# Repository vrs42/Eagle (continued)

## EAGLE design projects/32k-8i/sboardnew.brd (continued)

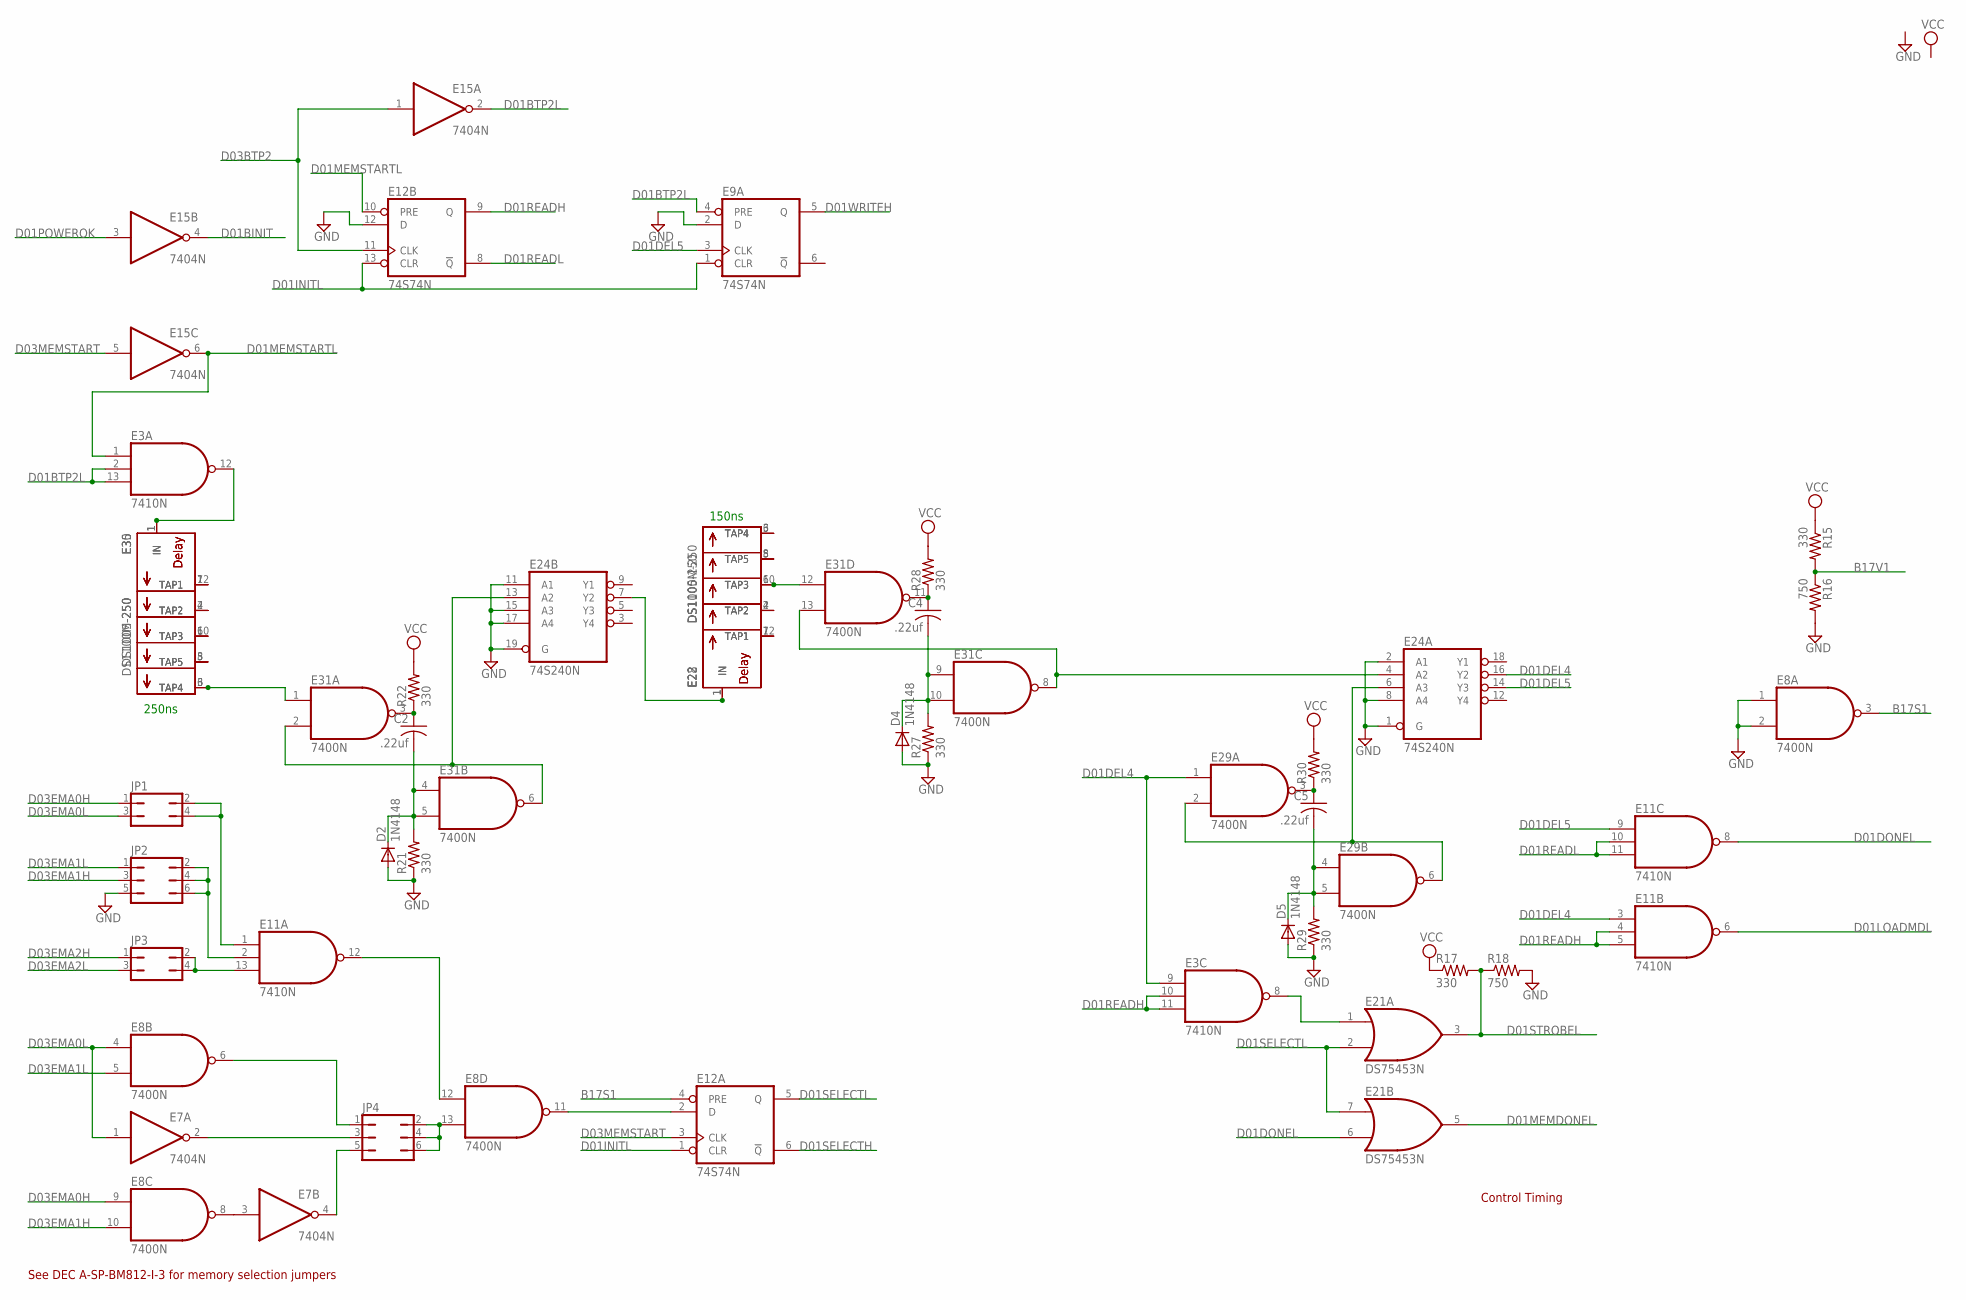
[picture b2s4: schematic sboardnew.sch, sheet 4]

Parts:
C2, C4, C5: .22uf; C050-025X075
D2, D4, D5: 1N4148; DO35-10
E3, E11: 7410N; DIL14
E7, E15: 7404N; DIL14
E8, E29, E31: 7400N; DIL14
E9, E12: 74S74N; DIL14
E21: DS75453N; DIL08
E22, E35: DS1100M-250; DIL08
E24: 74S240N; DIL20
E28, E30: DS1005-250; DIL14
JP1, JP3: JP2Q
JP2, JP4: JP3Q
R15, R17, R21, R22, R27, R28, R29, R30: 330; 0207/10
R16, R18: 750; 0207/10

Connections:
B17S1: E8.3 (O), E12.4 (PRE); also elsewhere on the board
B17V1: R15.2, R16.1; also elsewhere on the board
D01BINIT: E15.4 (O); also elsewhere on the board
D01BTP2L: E3.2 (I1), E3.13 (I2), E9.4 (PRE), E15.2 (O)
D01DEL2X: E22.1 (IN), E24.7 (Y2), E28.1 (IN)
D01DEL4: E3.9 (I0), E11.3 (I0), E24.16 (Y2), E29.1 (I0)
D01DEL5: E9.3 (CLK), E11.9 (I0), E24.14 (Y3)
D01DONEL: E11.8 (O), E21.6 (I1)
D01INITL: E9.1 (CLR), E12.1 (CLR), E12.13 (CLR); also elsewhere on the board
D01LOADMDL: E11.6 (O); also elsewhere on the board
D01MEMDONEL: E21.5 (O); also elsewhere on the board
D01MEMSTARTL: E3.1 (I0), E12.10 (PRE), E15.6 (O)
D01POWEROK: E15.3 (I); also elsewhere on the board
D01READH: E3.10 (I1), E3.11 (I2), E11.4 (I1), E11.5 (I2), E12.9 (Q)
D01READL: E11.10 (I1), E11.11 (I2), E12.8 (!Q); also elsewhere on the board
D01SELECTH: E12.6 (!Q); also elsewhere on the board
D01SELECTL: E12.5 (Q), E21.2 (I1), E21.7 (I0)
D01SELL: E8.11 (O), E12.2 (D)
D01STROBEL: E21.3 (O), R17.2, R18.1; also elsewhere on the board
D01WRITEH: E9.5 (Q); also elsewhere on the board
D03BTP2: E12.11 (CLK), E15.1 (I); also elsewhere on the board
D03EMA0H: E8.9 (I0), JP1.1; also elsewhere on the board
D03EMA0L: E7.1 (I), E8.4 (I0), JP1.3; also elsewhere on the board
D03EMA1H: E8.10 (I1), JP2.3; also elsewhere on the board
D03EMA1L: E8.5 (I1), JP2.1; also elsewhere on the board
D03EMA2H: JP3.1; also elsewhere on the board
D03EMA2L: JP3.3; also elsewhere on the board
D03MEMSTART: E12.3 (CLK), E15.5 (I); also elsewhere on the board
GND: D2.A, D4.A, D5.A, E3.7 (GND), E7.7 (GND), E8.1 (I0), E8.2 (I1), E8.7 (GND), E9.2 (D), E9.7 (GND), E11.7 (GND), E12.7 (GND), E12.12 (D), E15.7 (GND), E21.4 (GND), E22.4 (GND), E24.1 (G), E24.2 (A1), E24.8 (A4), E24.10 (GND), E24.11 (A1), E24.15 (A3), E24.17 (A4), E24.19 (G), E28.7 (GND), E29.7 (GND), E30.7 (GND), E31.7 (GND), E35.4 (GND), JP2.5, R16.2, R18.2, R21.1, R27.1, R29.1; also elsewhere on the board
unnamed: E22.2 (TAP2), E28.4 (TAP2)
unnamed: C5.2, D5.C, E29.4 (I0), E29.5 (I1), R29.2
unnamed: E8.13 (I1), JP4.2, JP4.4, JP4.6
unnamed: C2.2, D2.C, E31.4 (I0), E31.5 (I1), R21.2
unnamed: E30.12 (TAP1), E35.7 (TAP1)
unnamed: C2.1, E31.3 (O), R22.1
unnamed: E24.13 (A2), E31.2 (I1), E31.6 (O)
unnamed: E30.6 (TAP4), E31.1 (I0), E35.3 (TAP4)
unnamed: C4.2, D4.C, E31.9 (I0), E31.10 (I1), R27.2
unnamed: C4.1, E31.11 (O), R28.1
unnamed: E3.12 (O), E30.1 (IN), E35.1 (IN)
unnamed: E24.4 (A2), E31.8 (O), E31.13 (I1)
unnamed: E22.6 (TAP3), E28.10 (TAP3), E31.12 (I0)
unnamed: C5.1, E29.3 (O), R30.1
unnamed: E24.6 (A3), E29.2 (I1), E29.6 (O)
unnamed: E22.7 (TAP1), E28.12 (TAP1)
unnamed: E22.3 (TAP4), E28.6 (TAP4)
unnamed: E22.5 (TAP5), E28.8 (TAP5)
unnamed: E30.4 (TAP2), E35.2 (TAP2)
unnamed: E30.10 (TAP3), E35.6 (TAP3)
unnamed: E30.8 (TAP5), E35.5 (TAP5)
unnamed: E8.6 (O), JP4.1
unnamed: E3.8 (O), E21.1 (I0)
unnamed: E7.2 (O), JP4.3
unnamed: E7.3 (I), E8.8 (O)
unnamed: E7.4 (O), JP4.5
unnamed: E11.13 (I2), JP3.2, JP3.4
unnamed: E11.2 (I1), JP2.2, JP2.4, JP2.6
unnamed: E11.1 (I0), JP1.2, JP1.4
unnamed: E8.12 (I0), E11.12 (O)
VCC: E3.14 (VCC), E7.14 (VCC), E8.14 (VCC), E9.14 (VCC), E11.14 (VCC), E12.14 (VCC), E15.14 (VCC), E21.8 (VCC), E22.8 (VCC), E24.20 (VCC), E28.14 (VCC), E29.14 (VCC), E30.14 (VCC), E31.14 (VCC), E35.8 (VCC), R15.1, R17.1, R22.2, R28.2, R30.2; also elsewhere on the board

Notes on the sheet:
Control Timing
See DEC A-SP-BM812-I-3 for memory selection jumpers
250ns
150ns

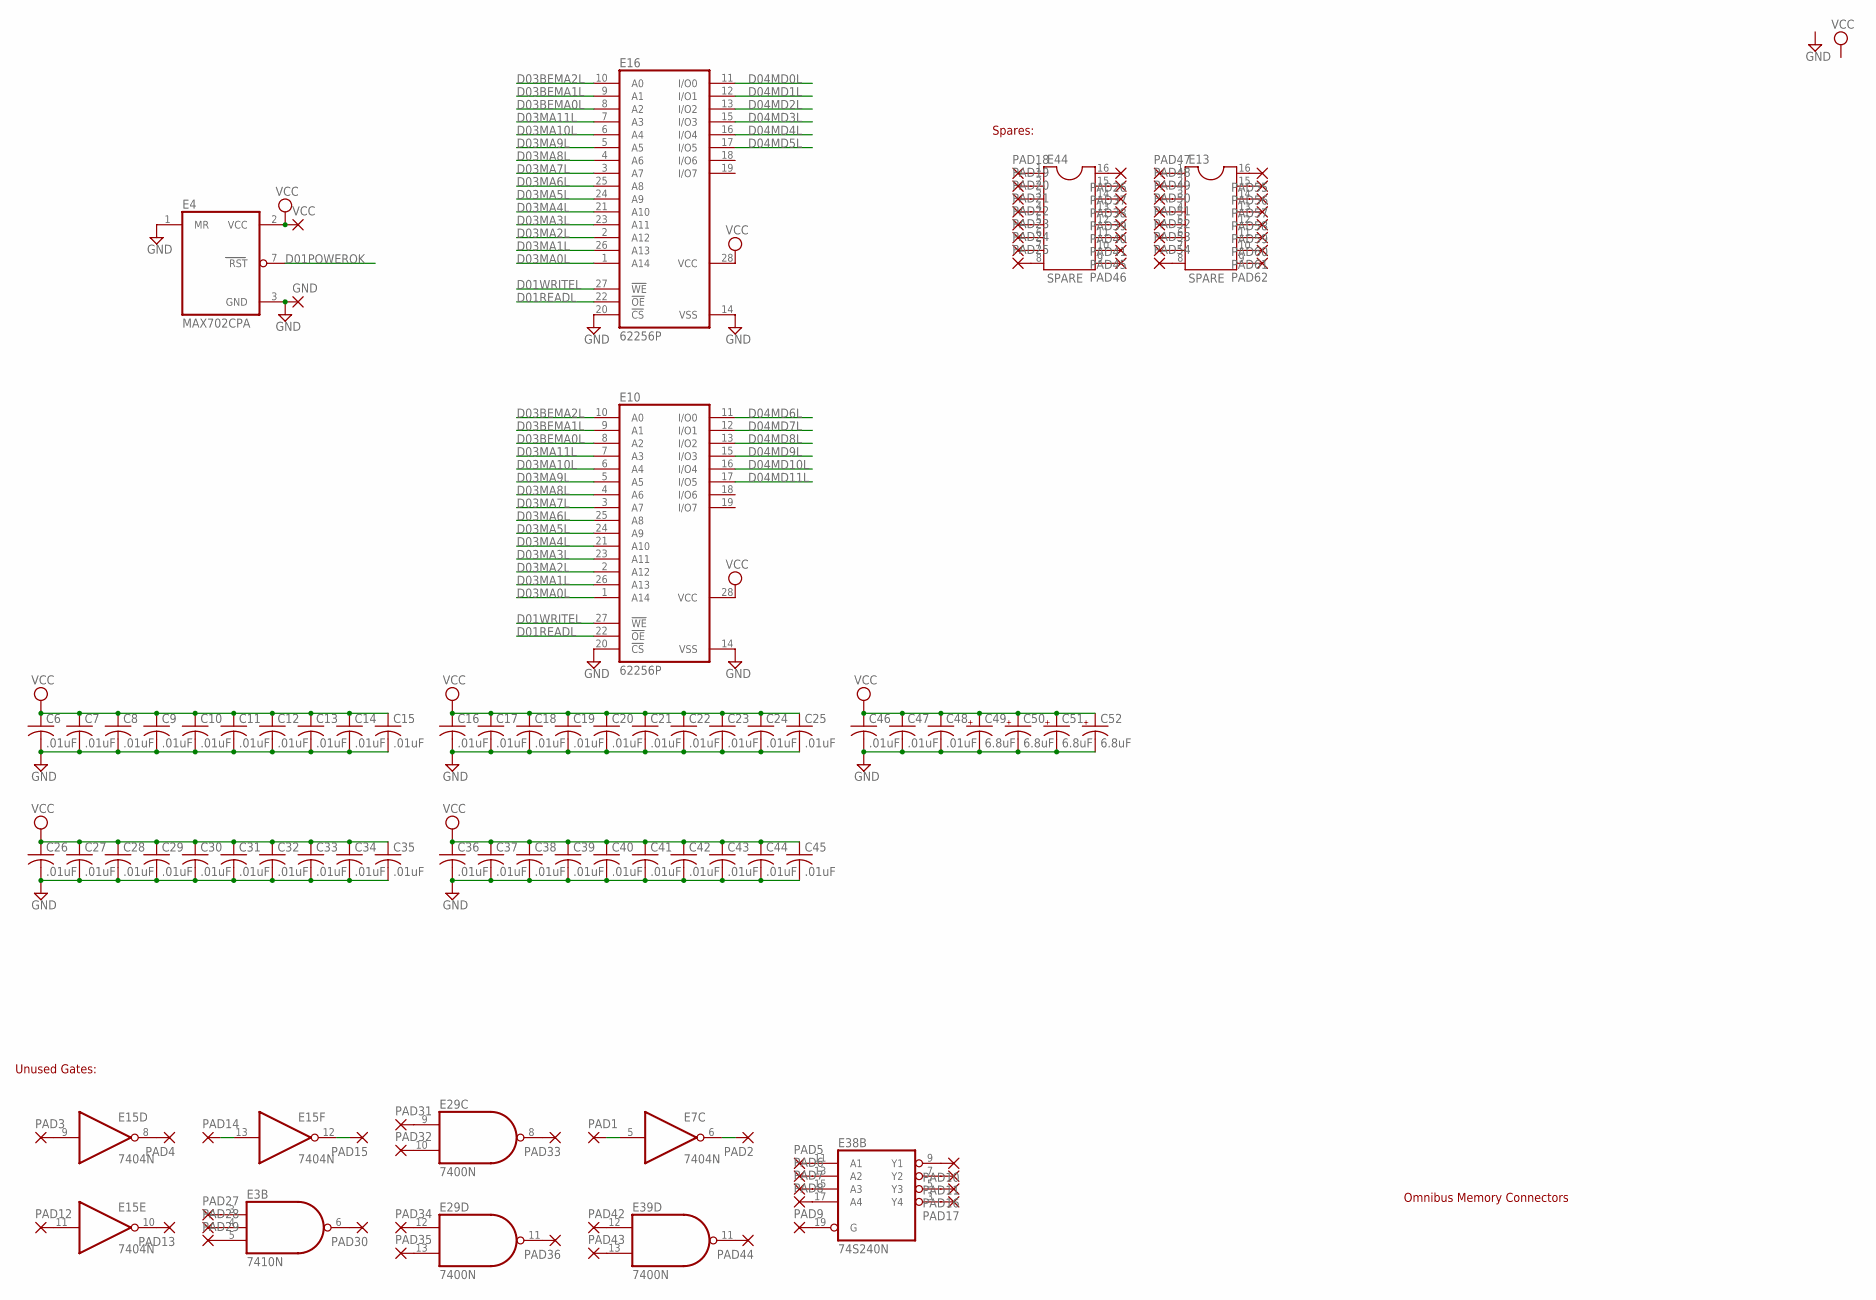
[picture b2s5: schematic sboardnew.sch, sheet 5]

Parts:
C6, C7, C8, C9, C10, C11, C12, C13, C14, C15, C16, C17, C18, C19, C20, C21, C22, C23, C24, C25, C26, C27, C28, C29, C30, C31, C32, C33, C34, C35, C36, C37, C38, C39, C40, C41, C42, C43, C44, C45, C46, C47, C48: .01uF; C050-025X075
C49, C50, C51, C52: 6.8uF; E22-6
E3: 7410N; DIL14
E4: MAX702CPA; DIL08
E7, E15: 7404N; DIL14
E10, E16: 62256P; DIL28-6
E13, E44: SPARE; DIL16
E29, E39: 7400N; DIL14
E38: 74S240N; DIL20
GND: 2,15/1,0
PAD1, PAD2, PAD3, PAD4, PAD5, PAD6, PAD7, PAD8, PAD9, PAD10, PAD11, PAD12, PAD13, PAD14, PAD15, PAD16, PAD17, PAD18, PAD19, PAD20, PAD21, PAD22, PAD23, PAD24, PAD25, PAD26, PAD27, PAD28, PAD29, PAD30, PAD31, PAD32, PAD33, PAD34, PAD35, PAD36, PAD37, PAD38, PAD39, PAD40, PAD41, PAD42, PAD43, PAD44, PAD45, PAD46, PAD47, PAD48, PAD49, PAD50, PAD51, PAD52, PAD53, PAD54, PAD55, PAD56, PAD57, PAD58, PAD59, PAD60, PAD61, PAD62: 1,6/0,8
VCC: 2,15/1,0

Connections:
D01POWEROK: E4.7 (RST); also elsewhere on the board
D01READL: E10.22 (!OE), E16.22 (!OE); also elsewhere on the board
D01WRITEL: E10.27 (!WE), E16.27 (!WE); also elsewhere on the board
D03BEMA0L: E10.8 (A2), E16.8 (A2); also elsewhere on the board
D03BEMA1L: E10.9 (A1), E16.9 (A1); also elsewhere on the board
D03BEMA2L: E10.10 (A0), E16.10 (A0); also elsewhere on the board
D03MA0L: E10.1 (A14), E16.1 (A14); also elsewhere on the board
D03MA1L: E10.26 (A13), E16.26 (A13); also elsewhere on the board
D03MA2L: E10.2 (A12), E16.2 (A12); also elsewhere on the board
D03MA3L: E10.23 (A11), E16.23 (A11); also elsewhere on the board
D03MA4L: E10.21 (A10), E16.21 (A10); also elsewhere on the board
D03MA5L: E10.24 (A9), E16.24 (A9); also elsewhere on the board
D03MA6L: E10.25 (A8), E16.25 (A8); also elsewhere on the board
D03MA7L: E10.3 (A7), E16.3 (A7); also elsewhere on the board
D03MA8L: E10.4 (A6), E16.4 (A6); also elsewhere on the board
D03MA9L: E10.5 (A5), E16.5 (A5); also elsewhere on the board
D03MA10L: E10.6 (A4), E16.6 (A4); also elsewhere on the board
D03MA11L: E10.7 (A3), E16.7 (A3); also elsewhere on the board
D04MD0L: E16.11 (I/O0); also elsewhere on the board
D04MD1L: E16.12 (I/O1); also elsewhere on the board
D04MD2L: E16.13 (I/O2); also elsewhere on the board
D04MD3L: E16.15 (I/O3); also elsewhere on the board
D04MD4L: E16.16 (I/O4); also elsewhere on the board
D04MD5L: E16.17 (I/O5); also elsewhere on the board
D04MD6L: E10.11 (I/O0); also elsewhere on the board
D04MD7L: E10.12 (I/O1); also elsewhere on the board
D04MD8L: E10.13 (I/O2); also elsewhere on the board
D04MD9L: E10.15 (I/O3); also elsewhere on the board
D04MD10L: E10.16 (I/O4); also elsewhere on the board
D04MD11L: E10.17 (I/O5); also elsewhere on the board
GND: C6.2, C7.2, C8.2, C9.2, C10.2, C11.2, C12.2, C13.2, C14.2, C15.2, C16.2, C17.2, C18.2, C19.2, C20.2, C21.2, C22.2, C23.2, C24.2, C25.2, C26.2, C27.2, C28.2, C29.2, C30.2, C31.2, C32.2, C33.2, C34.2, C35.2, C36.2, C37.2, C38.2, C39.2, C40.2, C41.2, C42.2, C43.2, C44.2, C45.2, C46.2, C47.2, C48.2, C49.-, C50.-, C51.-, C52.-, E3.7 (GND), E4.1 (MR), E4.3 (GND), E7.7 (GND), E10.14 (VSS), E10.20 (!CS), E15.7 (GND), E16.14 (VSS), E16.20 (!CS), E29.7 (GND), E38.10 (GND), E39.7 (GND), GND.1; also elsewhere on the board
unnamed: E7.5 (I), PAD1.1
unnamed: E7.6 (O), PAD2.1
unnamed: E15.9 (I), PAD3.1
unnamed: E15.8 (O), PAD4.1
unnamed: E38.11 (A1), PAD5.1
unnamed: E38.13 (A2), PAD6.1
unnamed: E38.15 (A3), PAD7.1
unnamed: E38.19 (G), PAD9.1
unnamed: E38.9 (Y1), PAD10.1
unnamed: E38.7 (Y2), PAD11.1
unnamed: E38.5 (Y3), PAD16.1
unnamed: E38.3 (Y4), PAD17.1
unnamed: E38.17 (A4), PAD8.1
unnamed: E44.1, PAD18.1
unnamed: E44.2, PAD19.1
unnamed: E44.3, PAD20.1
unnamed: E44.4, PAD21.1
unnamed: E15.11 (I), PAD12.1
unnamed: E15.10 (O), PAD13.1
unnamed: E15.13 (I), PAD14.1
unnamed: E15.12 (O), PAD15.1
unnamed: E44.5, PAD22.1
unnamed: E44.6, PAD23.1
unnamed: E44.7, PAD24.1
unnamed: E44.8, PAD25.1
unnamed: E44.16, PAD26.1
unnamed: E44.15, PAD37.1
unnamed: E44.14, PAD38.1
unnamed: E44.13, PAD39.1
unnamed: E44.12, PAD40.1
unnamed: E44.11, PAD41.1
unnamed: E44.10, PAD45.1
unnamed: E3.3 (I0), PAD27.1
unnamed: E3.4 (I1), PAD28.1
unnamed: E3.5 (I2), PAD29.1
unnamed: E3.6 (O), PAD30.1
unnamed: E29.9 (I0), PAD31.1
unnamed: E29.10 (I1), PAD32.1
unnamed: E29.8 (O), PAD33.1
unnamed: E29.12 (I0), PAD34.1
unnamed: E29.13 (I1), PAD35.1
unnamed: E29.11 (O), PAD36.1
unnamed: E44.9, PAD46.1
unnamed: E13.1, PAD47.1
unnamed: E13.2, PAD48.1
unnamed: E13.3, PAD49.1
unnamed: E13.4, PAD50.1
unnamed: E39.12 (I0), PAD42.1
unnamed: E39.13 (I1), PAD43.1
unnamed: E39.11 (O), PAD44.1
unnamed: E13.5, PAD51.1
unnamed: E13.6, PAD52.1
unnamed: E13.7, PAD53.1
unnamed: E13.8, PAD54.1
unnamed: E13.16, PAD55.1
unnamed: E13.15, PAD56.1
unnamed: E13.14, PAD57.1
unnamed: E13.13, PAD58.1
unnamed: E13.12, PAD59.1
unnamed: E13.11, PAD60.1
unnamed: E13.10, PAD61.1
unnamed: E13.9, PAD62.1
VCC: C6.1, C7.1, C8.1, C9.1, C10.1, C11.1, C12.1, C13.1, C14.1, C15.1, C16.1, C17.1, C18.1, C19.1, C20.1, C21.1, C22.1, C23.1, C24.1, C25.1, C26.1, C27.1, C28.1, C29.1, C30.1, C31.1, C32.1, C33.1, C34.1, C35.1, C36.1, C37.1, C38.1, C39.1, C40.1, C41.1, C42.1, C43.1, C44.1, C45.1, C46.1, C47.1, C48.1, C49.+, C50.+, C51.+, C52.+, E3.14 (VCC), E4.2 (VCC), E7.14 (VCC), E10.28 (VCC), E15.14 (VCC), E16.28 (VCC), E29.14 (VCC), E38.20 (VCC), E39.14 (VCC), VCC.1; also elsewhere on the board

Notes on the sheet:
Omnibus Memory Connectors
Unused Gates:
Spares:

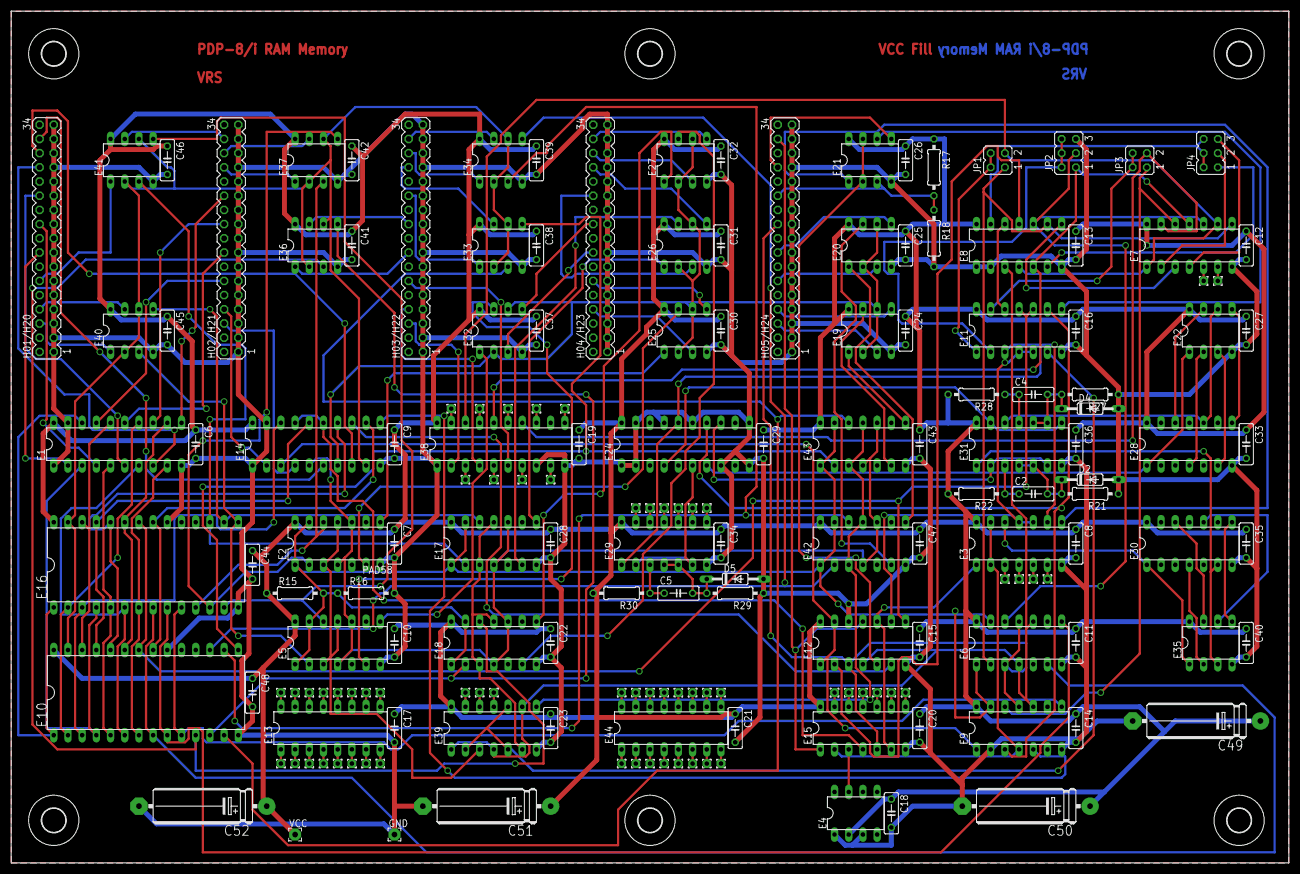
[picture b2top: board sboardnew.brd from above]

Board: 2 copper layers, 228.6 x 152.4 mm, 185 parts (0 on the bottom side), 206 nets.

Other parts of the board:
U$20, U$66, U$67, U$82, U$83, U$86: 4,3

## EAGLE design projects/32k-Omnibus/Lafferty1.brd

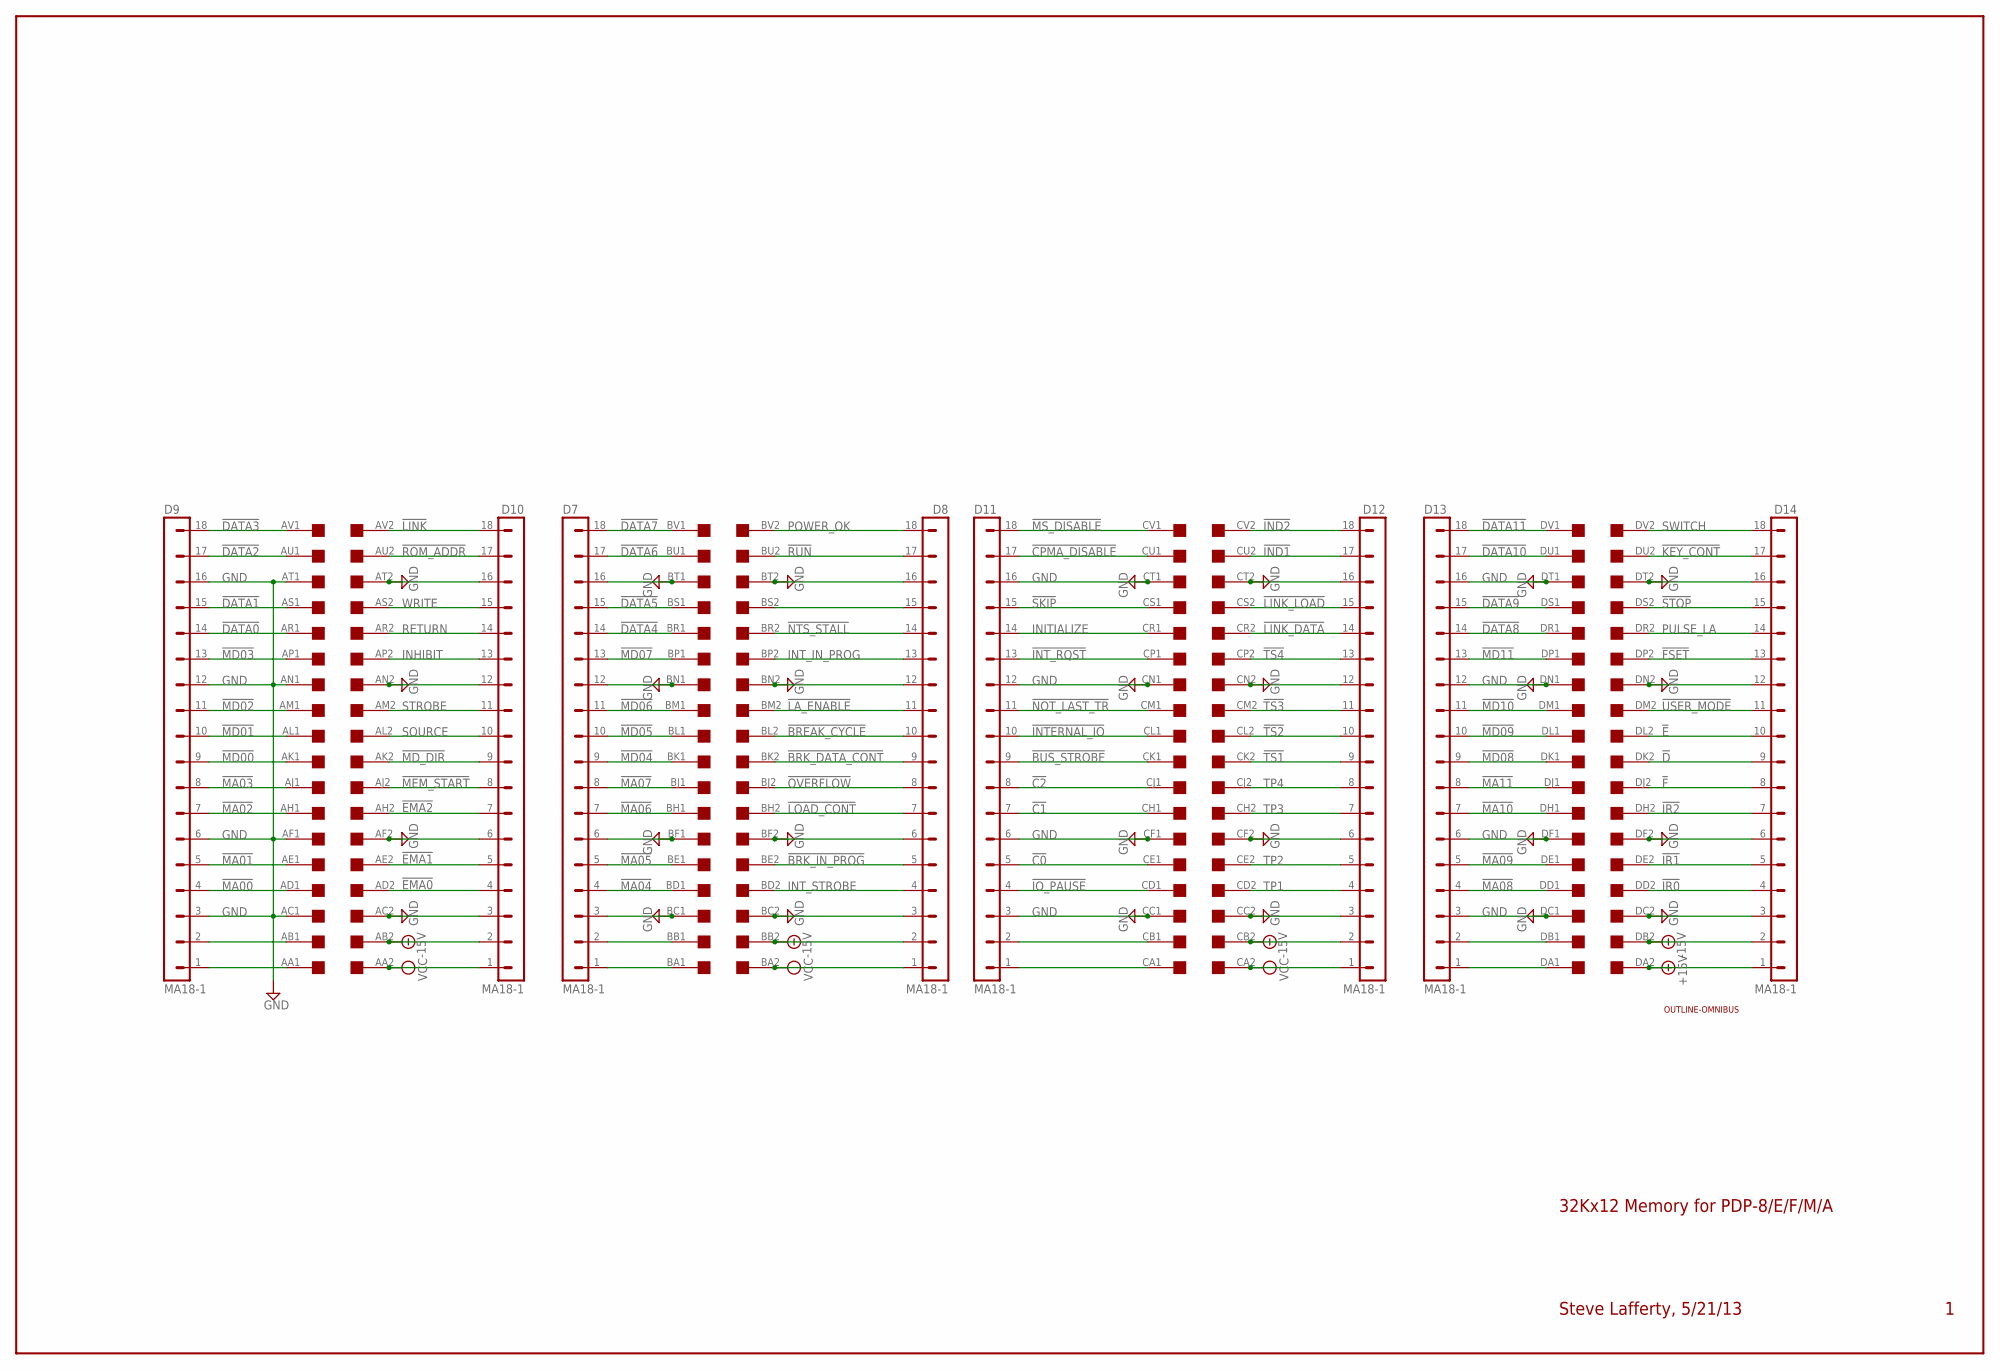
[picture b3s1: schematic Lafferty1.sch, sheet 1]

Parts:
D7, D8, D9, D10, D11, D12, D13, D14: MA18-1
U$1: OUTLINE-OMNIBUS; OMNIBUS
U$2: QUAD; EDGE-CON8

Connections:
!BREAK_CYCLE: D8.10, U$2.BL2
!BRK_DATA_CONT: D8.9, U$2.BK2
!BRK_IN_PROG: D8.5, U$2.BE2
!BUS_STROBE: D11.9, U$2.CK1
!C0: D11.5, U$2.CE1
!C1: D11.7, U$2.CH1
!C2: D11.8, U$2.CJ1
!CPMA_DISABLE: D11.17, U$2.CU1
!D: D14.9, U$2.DK2
!DATA0: D9.14, U$2.AR1
!DATA1: D9.15, U$2.AS1
!DATA2: D9.17, U$2.AU1
!DATA3: D9.18, U$2.AV1
!DATA4: D7.14, U$2.BR1
!DATA5: D7.15, U$2.BS1
!DATA6: D7.17, U$2.BU1
!DATA7: D7.18, U$2.BV1
!DATA8: D13.14, U$2.DR1
!DATA9: D13.15, U$2.DS1
!DATA10: D13.17, U$2.DU1
!DATA11: D13.18, U$2.DV1
!E: D14.10, U$2.DL2
!EMA0: D10.4, U$2.AD2; also elsewhere on the board
!EMA1: D10.5, U$2.AE2; also elsewhere on the board
!EMA2: D10.7, U$2.AH2; also elsewhere on the board
!F: D14.8, U$2.DJ2
!FSET: D14.13, U$2.DP2
!IND1: D12.17, U$2.CU2
!IND2: D12.18, U$2.CV2
!INTERNAL_IO: D11.10, U$2.CL1
!INT_RQST: D11.13, U$2.CP1
!IO_PAUSE: D11.4, U$2.CD1
!IR0: D14.4, U$2.DD2
!IR1: D14.5, U$2.DE2
!IR2: D14.7, U$2.DH2
!KEY_CONT: D14.17, U$2.DU2
!LA_ENABLE: D8.11, U$2.BM2
!LINK: D10.18, U$2.AV2
!LINK_DATA: D12.14, U$2.CR2
!LINK_LOAD: D12.15, U$2.CS2
!LOAD_CONT: D8.7, U$2.BH2
!MA00: D9.4, U$2.AD1; also elsewhere on the board
!MA01: D9.5, U$2.AE1; also elsewhere on the board
!MA02: D9.7, U$2.AH1; also elsewhere on the board
!MA03: D9.8, U$2.AJ1; also elsewhere on the board
!MA04: D7.4, U$2.BD1; also elsewhere on the board
!MA05: D7.5, U$2.BE1; also elsewhere on the board
!MA06: D7.7, U$2.BH1; also elsewhere on the board
!MA07: D7.8, U$2.BJ1; also elsewhere on the board
!MA08: D13.4, U$2.DD1; also elsewhere on the board
!MA09: D13.5, U$2.DE1; also elsewhere on the board
!MA10: D13.7, U$2.DH1; also elsewhere on the board
!MA11: D13.8, U$2.DJ1; also elsewhere on the board
!MD00: D9.9, U$2.AK1; also elsewhere on the board
!MD01: D9.10, U$2.AL1; also elsewhere on the board
!MD02: D9.11, U$2.AM1; also elsewhere on the board
!MD03: D9.13, U$2.AP1; also elsewhere on the board
!MD04: D7.9, U$2.BK1; also elsewhere on the board
!MD05: D7.10, U$2.BL1; also elsewhere on the board
!MD06: D7.11, U$2.BM1; also elsewhere on the board
!MD07: D7.13, U$2.BP1; also elsewhere on the board
!MD08: D13.9, U$2.DK1; also elsewhere on the board
!MD09: D13.10, U$2.DL1; also elsewhere on the board
!MD10: D13.11, U$2.DM1; also elsewhere on the board
!MD11: D13.13, U$2.DP1; also elsewhere on the board
!MD_DIR: D10.9, U$2.AK2; also elsewhere on the board
!MEM_START: D10.8, U$2.AJ2
!MS_DISABLE: D11.18, U$2.CV1
!NOT_LAST_TR: D11.11, U$2.CM1
!NTS_STALL: D8.14, U$2.BR2
!OVERFLOW: D8.8, U$2.BJ2
!ROM_ADDR: D10.17, U$2.AU2; also elsewhere on the board
!RUN: D8.17, U$2.BU2
!SKIP: D11.15, U$2.CS1
!STOP: D14.15, U$2.DS2
!TS1: D12.9, U$2.CK2
!TS2: D12.10, U$2.CL2
!TS3: D12.11, U$2.CM2
!TS4: D12.13, U$2.CP2
!USER_MODE: D14.11, U$2.DM2
+15V: D14.1, U$2.DA2
-15V: D8.2, D10.2, D12.2, D14.2, U$2.AB2, U$2.BB2, U$2.CB2, U$2.DB2
GND: D7.3, D7.6, D7.12, D7.16, D8.3, D8.6, D8.12, D8.16, D9.3, D9.6, D9.12, D9.16, D10.3, D10.6, D10.12, D10.16, D11.3, D11.6, D11.12, D11.16, D12.3, D12.6, D12.12, D12.16, D13.3, D13.6, D13.12, D13.16, D14.3, D14.6, D14.12, D14.16, U$2.AC1, U$2.AC2, U$2.AF1, U$2.AF2, U$2.AN1, U$2.AN2, U$2.AT1, U$2.AT2, U$2.BC1, U$2.BC2, U$2.BF1, U$2.BF2, U$2.BN1, U$2.BN2, U$2.BT1, U$2.BT2, U$2.CC1, U$2.CC2, U$2.CF1, U$2.CF2, U$2.CN1, U$2.CN2, U$2.CT1, U$2.CT2, U$2.DC1, U$2.DC2, U$2.DF1, U$2.DF2, U$2.DN1, U$2.DN2, U$2.DT1, U$2.DT2; also elsewhere on the board
INHIBIT: D10.13, U$2.AP2
INITIALIZE: D11.14, U$2.CR1
INT_IN_PROG: D8.13, U$2.BP2
INT_STROBE: D8.4, U$2.BD2
unnamed: D9.2, U$2.AB1
unnamed: D9.1, U$2.AA1
unnamed: D7.2, U$2.BB1
unnamed: D7.1, U$2.BA1
unnamed: D11.1, U$2.CA1
unnamed: D8.15, U$2.BS2
unnamed: D11.2, U$2.CB1
unnamed: D13.1, U$2.DA1
unnamed: D13.2, U$2.DB1
POWER_OK: D8.18, U$2.BV2; also elsewhere on the board
PULSE_LA: D14.14, U$2.DR2
RETURN: D10.14, U$2.AR2
SOURCE: D10.10, U$2.AL2; also elsewhere on the board
STROBE: D10.11, U$2.AM2
SWITCH: D14.18, U$2.DV2
TP1: D12.4, U$2.CD2
TP2: D12.5, U$2.CE2
TP3: D12.7, U$2.CH2
TP4: D12.8, U$2.CJ2
VCC: D8.1, D10.1, D12.1, U$2.AA2, U$2.BA2, U$2.CA2; also elsewhere on the board
WRITE: D10.15, U$2.AS2; also elsewhere on the board

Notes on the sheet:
32Kx12 Memory for PDP-8/E/F/M/A
Steve Lafferty, 5/21/13

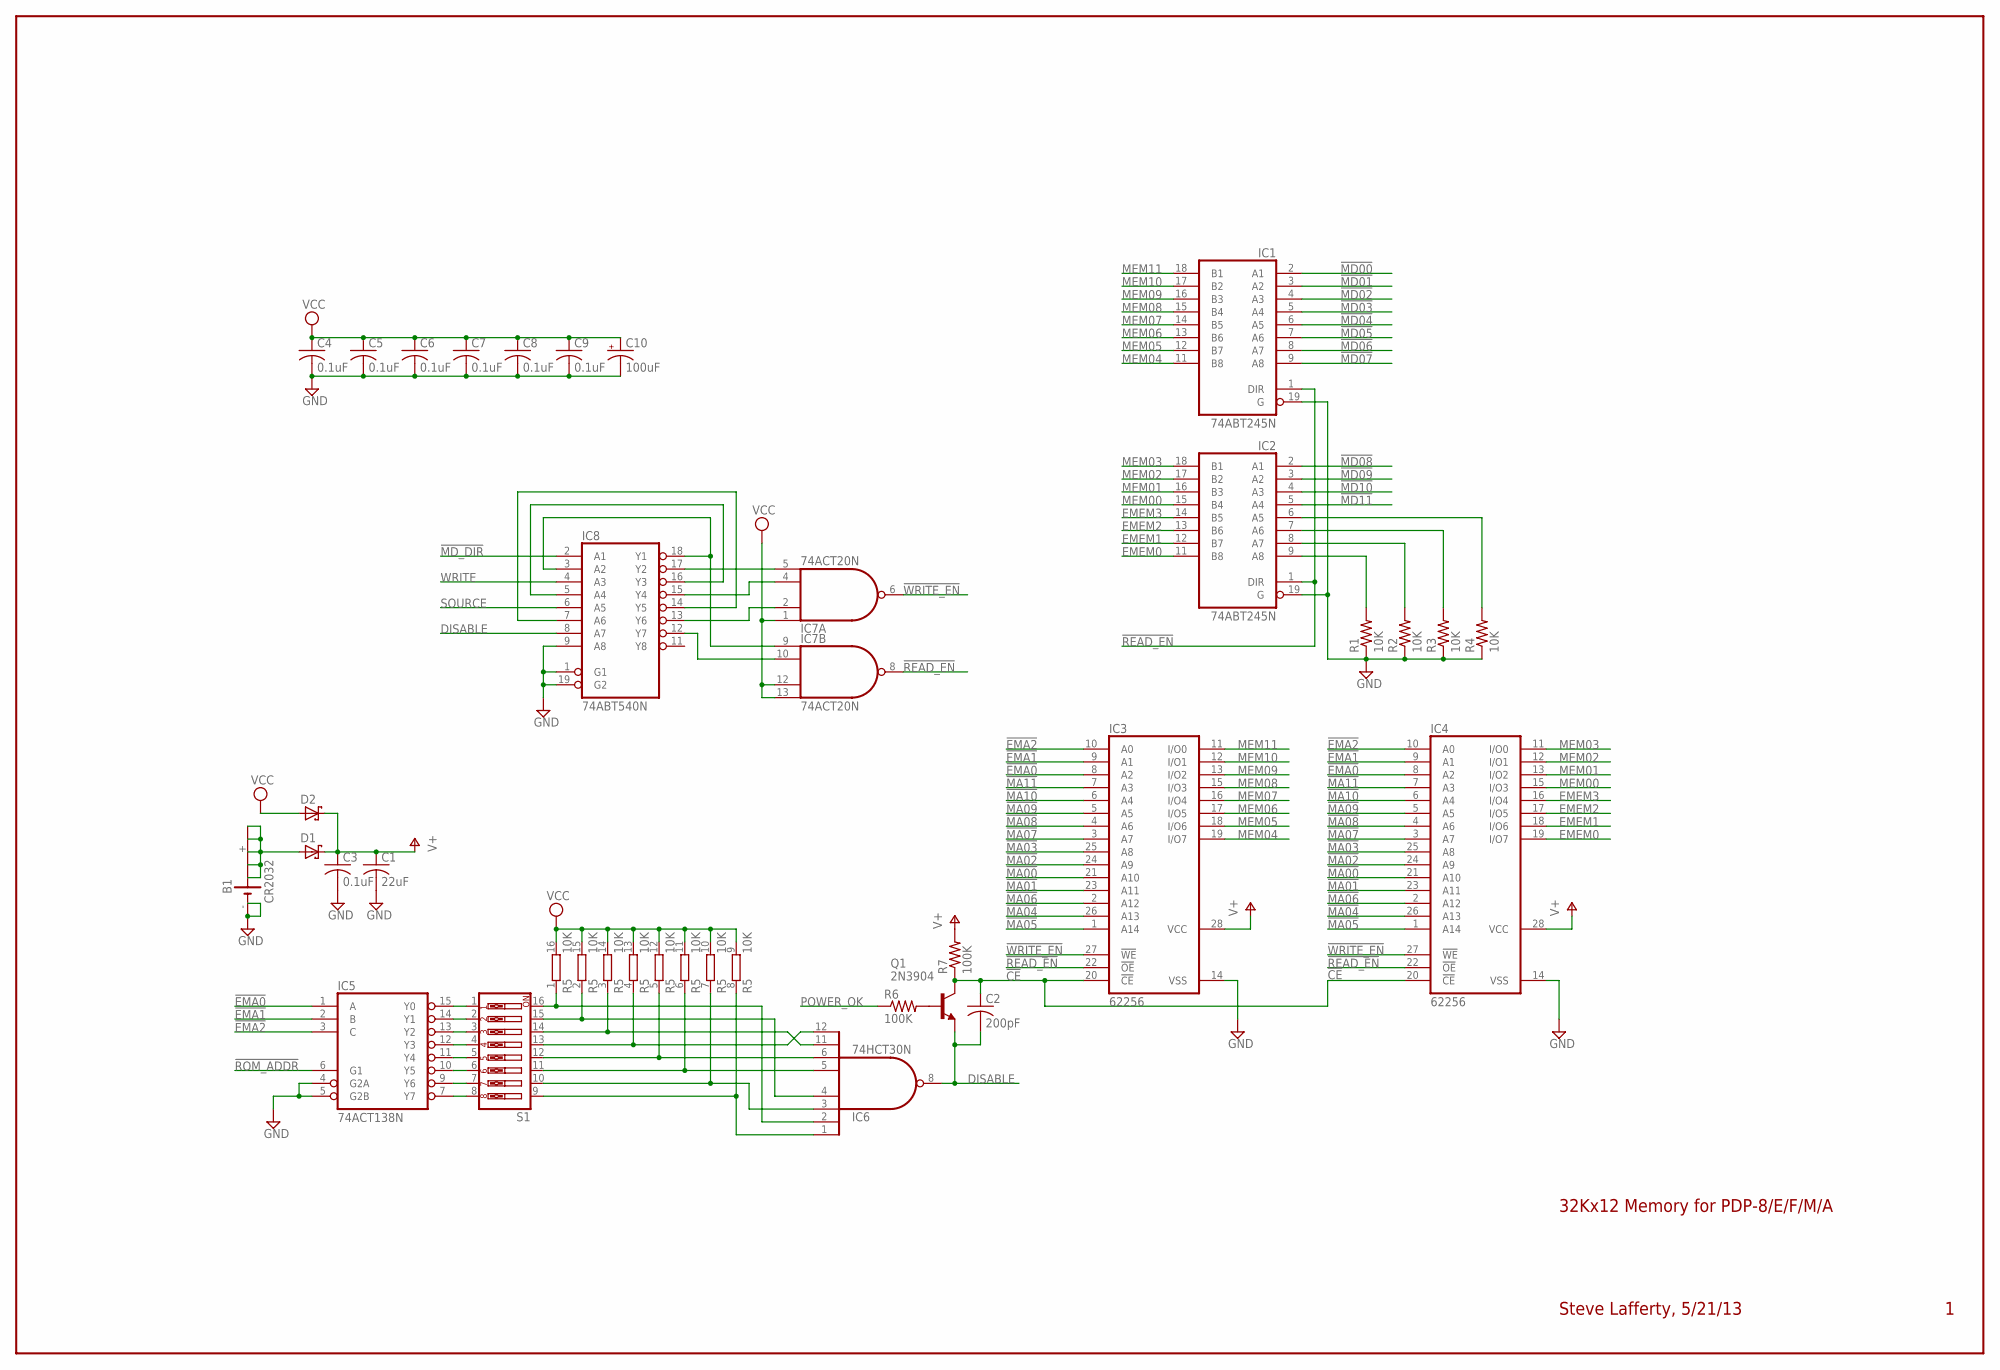
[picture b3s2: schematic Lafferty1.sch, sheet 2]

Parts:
B1: CR2032; B2430UNI
C1: 22uF; C050-025X075
C2: 200pF; C050-025X075
C3, C4, C5, C6, C7, C8, C9: 0.1uF; C050-025X075
C10: 100uF; E12-8
D1, D2: BAT19; DO35-10
IC1, IC2: 74ABT245N; DIL20
IC3, IC4: 62256; DIL28-6
IC5: 74ACT138N; DIL16
IC6: 74HCT30N; DIL14
IC7: 74ACT20N; DIL14
IC8: 74ABT540N; DIL20
Q1: 2N3904; TO92
R1, R2, R3, R4: 10K; 0207/10
R5: 10K; DIL16
R6, R7: 100K; 0207/10
S1: SW_DIP-8; EDG-08

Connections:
!CE: C2.1, IC3.20 (!CE), IC4.20 (!CE), Q1.1 (C), R7.1
!EMA0: IC3.8 (A2), IC4.8 (A2), IC5.1 (A); also elsewhere on the board
!EMA1: IC3.9 (A1), IC4.9 (A1), IC5.2 (B); also elsewhere on the board
!EMA2: IC3.10 (A0), IC4.10 (A0), IC5.3 (C); also elsewhere on the board
!MA00: IC3.21 (A10), IC4.21 (A10); also elsewhere on the board
!MA01: IC3.23 (A11), IC4.23 (A11); also elsewhere on the board
!MA02: IC3.24 (A9), IC4.24 (A9); also elsewhere on the board
!MA03: IC3.25 (A8), IC4.25 (A8); also elsewhere on the board
!MA04: IC3.26 (A13), IC4.26 (A13); also elsewhere on the board
!MA05: IC3.1 (A14), IC4.1 (A14); also elsewhere on the board
!MA06: IC3.2 (A12), IC4.2 (A12); also elsewhere on the board
!MA07: IC3.3 (A7), IC4.3 (A7); also elsewhere on the board
!MA08: IC3.4 (A6), IC4.4 (A6); also elsewhere on the board
!MA09: IC3.5 (A5), IC4.5 (A5); also elsewhere on the board
!MA10: IC3.6 (A4), IC4.6 (A4); also elsewhere on the board
!MA11: IC3.7 (A3), IC4.7 (A3); also elsewhere on the board
!MD00: IC1.2 (A1); also elsewhere on the board
!MD01: IC1.3 (A2); also elsewhere on the board
!MD02: IC1.4 (A3); also elsewhere on the board
!MD03: IC1.5 (A4); also elsewhere on the board
!MD04: IC1.6 (A5); also elsewhere on the board
!MD05: IC1.7 (A6); also elsewhere on the board
!MD06: IC1.8 (A7); also elsewhere on the board
!MD07: IC1.9 (A8); also elsewhere on the board
!MD08: IC2.2 (A1); also elsewhere on the board
!MD09: IC2.3 (A2); also elsewhere on the board
!MD10: IC2.4 (A3); also elsewhere on the board
!MD11: IC2.5 (A4); also elsewhere on the board
!MD_DIR: IC8.2 (A1); also elsewhere on the board
!READ_EN: IC1.1 (DIR), IC2.1 (DIR), IC3.22 (!OE), IC4.22 (!OE), IC7.8 (O)
!ROM_ADDR: IC5.6 (G1); also elsewhere on the board
!WRITE_EN: IC3.27 (!WE), IC4.27 (!WE), IC7.6 (O)
DISABLE: C2.2, IC6.8 (O), IC8.8 (A7), Q1.3 (E)
EMEM0: IC2.11 (B8), IC4.19 (I/O7)
EMEM1: IC2.12 (B7), IC4.18 (I/O6)
EMEM2: IC2.13 (B6), IC4.17 (I/O5)
EMEM3: IC2.14 (B5), IC4.16 (I/O4)
GND: B1.-, B1.-@1 (-), C1.2, C3.2, C4.2, C5.2, C6.2, C7.2, C8.2, C9.2, C10.-, IC1.10 (GND), IC1.19 (G), IC2.10 (GND), IC2.19 (G), IC3.14 (VSS), IC4.14 (VSS), IC5.4 (G2A), IC5.5 (G2B), IC5.8 (GND), IC6.7 (GND), IC7.7 (GND), IC8.1 (G1), IC8.9 (A8), IC8.10 (GND), IC8.19 (G2), R1.1, R2.1, R3.1, R4.1; also elsewhere on the board
MEM00: IC2.15 (B4), IC4.15 (I/O3)
MEM01: IC2.16 (B3), IC4.13 (I/O2)
MEM02: IC2.17 (B2), IC4.12 (I/O1)
MEM03: IC2.18 (B1), IC4.11 (I/O0)
MEM04: IC1.11 (B8), IC3.19 (I/O7)
MEM05: IC1.12 (B7), IC3.18 (I/O6)
MEM06: IC1.13 (B6), IC3.17 (I/O5)
MEM07: IC1.14 (B5), IC3.16 (I/O4)
MEM08: IC1.15 (B4), IC3.15 (I/O3)
MEM09: IC1.16 (B3), IC3.13 (I/O2)
MEM10: IC1.17 (B2), IC3.12 (I/O1)
MEM11: IC1.18 (B1), IC3.11 (I/O0)
unnamed: IC5.7 (Y7), S1.8
unnamed: IC5.9 (Y6), S1.7
unnamed: IC5.10 (Y5), S1.6
unnamed: IC5.11 (Y4), S1.5
unnamed: IC5.12 (Y3), S1.4
unnamed: IC5.13 (Y2), S1.3
unnamed: IC5.14 (Y1), S1.2
unnamed: IC5.15 (Y0), S1.1
unnamed: B1.+, B1.+@1 (+), B1.+@2 (+), B1.+@3 (+), B1.+@4 (+), D1.A
unnamed: IC6.12 (I7), R5.4 (1), S1.13
unnamed: IC6.11 (I6), R5.3 (1), S1.14
unnamed: IC6.6 (I5), R5.5 (1), S1.12
unnamed: IC6.5 (I4), R5.6 (1), S1.11
unnamed: IC6.3 (I2), R5.7 (1), S1.10
unnamed: IC6.1 (I0), R5.8 (1), S1.9
unnamed: IC6.2 (I1), R5.1, S1.16
unnamed: IC6.4 (I3), R5.2 (1), S1.15
unnamed: IC7.5 (I3), IC8.17 (Y2)
unnamed: IC2.6 (A5), R4.2
unnamed: Q1.2 (B), R6.2
unnamed: IC2.7 (A6), R3.2
unnamed: IC2.8 (A7), R2.2
unnamed: IC2.9 (A8), R1.2
unnamed: IC8.5 (A4), IC8.16 (Y3)
unnamed: IC7.9 (I0), IC8.3 (A2), IC8.18 (Y1)
unnamed: IC8.7 (A6), IC8.14 (Y5)
unnamed: IC7.2 (I1), IC8.13 (Y6)
unnamed: IC7.4 (I2), IC8.15 (Y4)
unnamed: IC7.10 (I1), IC8.12 (Y7)
POWER_OK: R6.1; also elsewhere on the board
SOURCE: IC8.6 (A5); also elsewhere on the board
V+: C1.1, C3.1, D1.C, D2.C, IC3.28 (VCC), IC4.28 (VCC), R7.2
VCC: C4.1, C5.1, C6.1, C7.1, C8.1, C9.1, C10.+, D2.A, IC1.20 (VCC), IC2.20 (VCC), IC5.16 (VCC), IC6.14 (VCC), IC7.1 (I0), IC7.12 (I2), IC7.13 (I3), IC7.14 (VCC), IC8.20 (VCC), R5.9 (2), R5.10 (2), R5.11 (2), R5.12 (2), R5.13 (2), R5.14 (2), R5.15 (2), R5.16 (2); also elsewhere on the board
WRITE: IC8.4 (A3); also elsewhere on the board

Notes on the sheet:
32Kx12 Memory for PDP-8/E/F/M/A
Steve Lafferty, 5/21/13
